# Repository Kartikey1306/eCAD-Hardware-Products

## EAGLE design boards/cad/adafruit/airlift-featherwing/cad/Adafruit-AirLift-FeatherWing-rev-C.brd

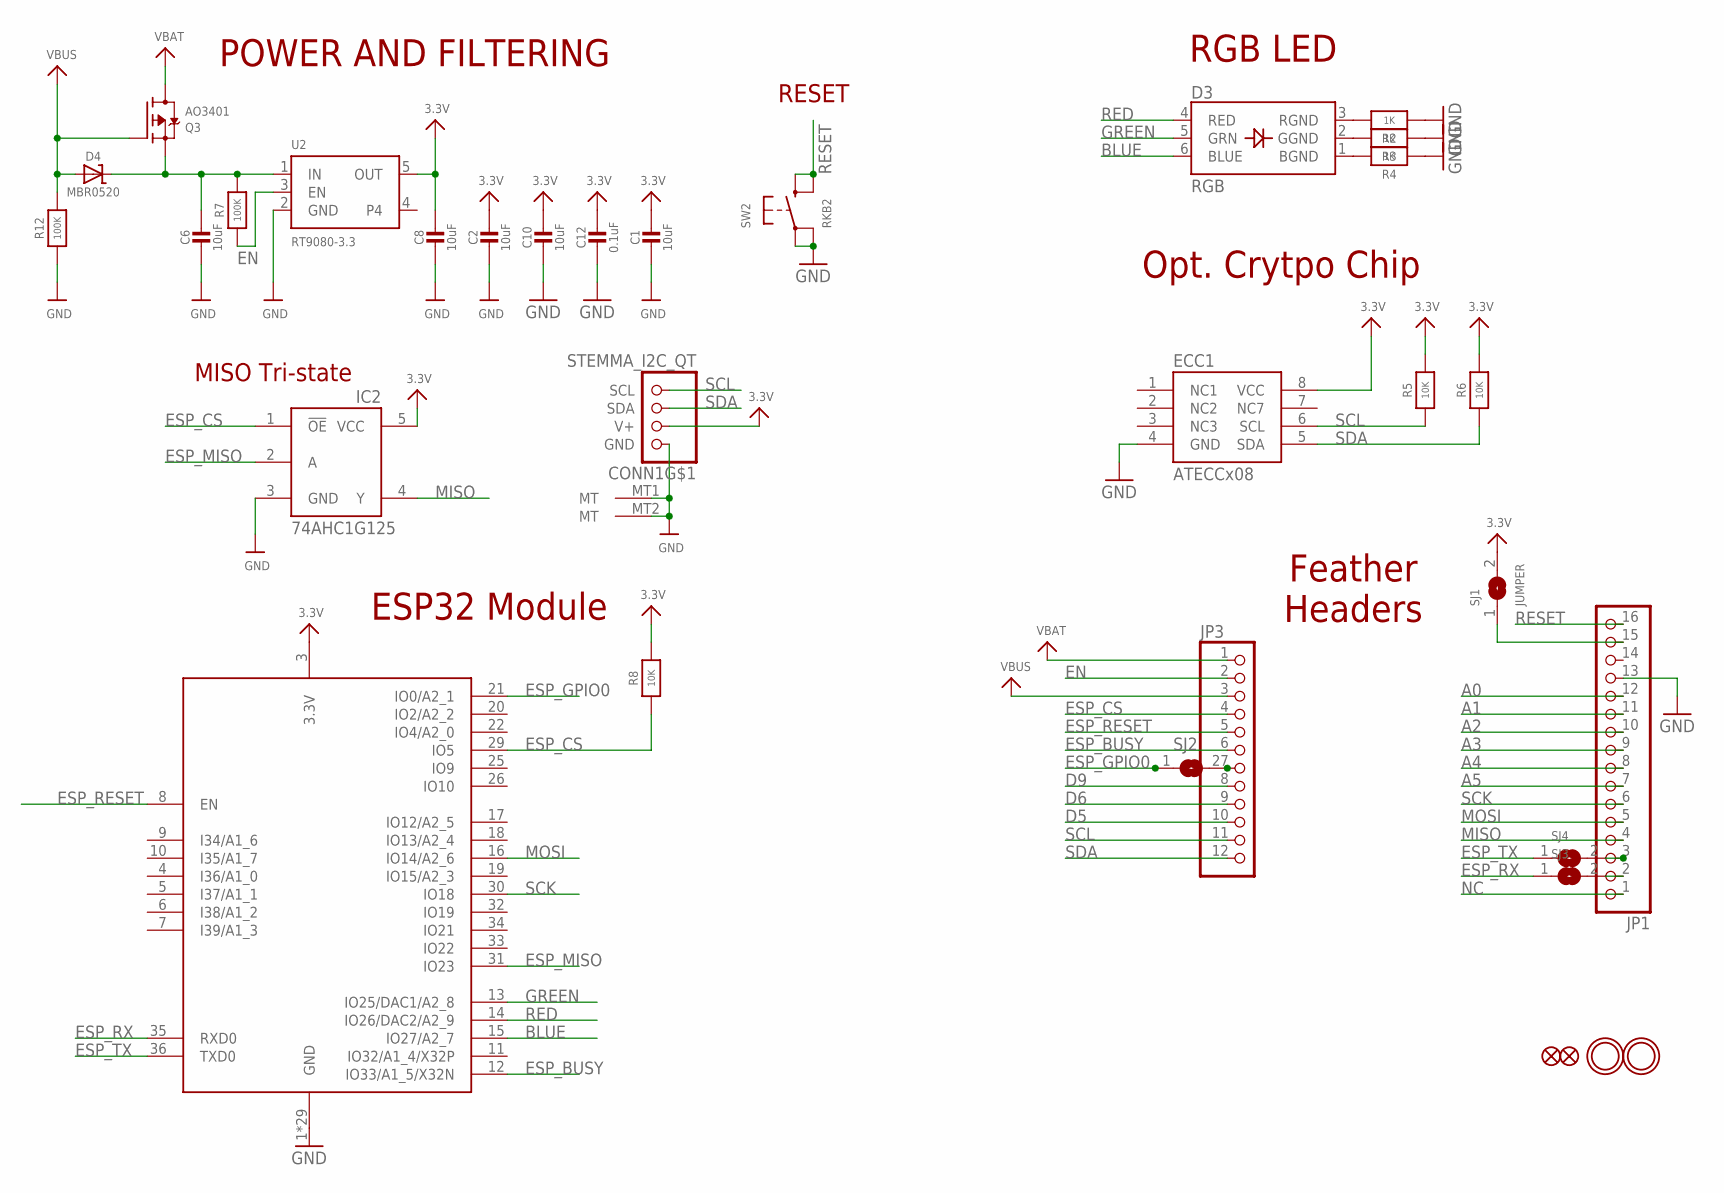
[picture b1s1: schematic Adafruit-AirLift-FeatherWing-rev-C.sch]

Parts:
C1, C2, C6, C8, C10: 10uF; 0805-NO
C12: 0.1uF; 0603-NO
CONN1: STEMMA_I2C_QT; JST_SH4
D3: RGB; RGBLED_3535_PLCC6
D4: MBR0520; SOD-123
ECC1: ATECCx08; SOIC8
IC2: 74AHC1G125; SOT23-5L
JP1: HEADER-1X16_MIN; 1X16_ROUND_MIN
JP3: HEADER-1X12_MIN; 1X12_ROUND_MIN
Q3: AO3401; SOT23-R
R2, R3, R4: 1K; 0603-NO
R5, R6, R8: 10K; 0603-NO
R7, R12: 100K; 0603-NO
SJ1: JUMPER; SOLDERJUMPER_ARROW_NOPASTE
SJ2, SJ3, SJ4: SOLDERJUMPER; SOLDERJUMPER_ARROW_NOPASTE
SW2: RKB2; BTN_RKB2_4.6X2.8
U2: RT9080-3.3; SOT23-5; JLC_ROTATION 0
U$31, U$32: MOUNTINGHOLE2.5; MOUNTINGHOLE_2.5_PLATED
U$34, U$35: FIDUCIAL_1MM
X1: ESP32-MINI-1

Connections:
3.3V: C1.1, C2.1, C8.1, C10.1, C12.1, CONN1.2 (V+), ECC1.8 (VCC), IC2.5 (VCC), R5.2, R6.2, R8.2, SJ1.2, U2.5 (OUT), X1.3 (3.3V)
A0: JP1.12
A1: JP1.11
A2: JP1.10
A3: JP1.9
A4: JP1.8
A5: JP1.7
BLUE: D3.6 (BLUE), X1.15 (IO27/A2_7)
D5: JP3.10
D6: JP3.9
D9: JP3.8
EN: JP3.2, R7.1, U2.3 (EN)
ESP_BUSY: JP3.6, X1.12 (IO33/A1_5/X32N)
ESP_CS: IC2.1 (!OE), JP3.4, R8.1, X1.29 (IO5)
ESP_GPIO0: SJ2.1, X1.21 (IO0/A2_1)
ESP_MISO: IC2.2 (A), X1.31 (IO23)
ESP_RESET: JP3.5, X1.8 (EN)
ESP_RX: SJ3.1, X1.35 (RXD0)
ESP_TX: SJ4.1, X1.36 (TXD0)
GND: C1.2, C2.2, C6.2, C8.2, C10.2, C12.2, CONN1.1 (GND), CONN1.MT1 (MT), CONN1.MT2 (MT), ECC1.4 (GND), IC2.3 (GND), JP1.13, R2.1, R3.1, R4.1, R12.1, SW2.A, SW2.A' (P1), U2.2 (GND), X1.1 (GND), X1.2 (GND), X1.27 (GND), X1.38 (GND), X1.39 (GND), X1.40 (GND), X1.41 (GND), X1.42 (GND), X1.43 (GND), X1.44 (GND), X1.45 (GND), X1.46 (GND), X1.47 (GND), X1.48 (GND), X1.49 (GND), X1.50 (GND), X1.51 (GND), X1.52 (GND), X1.53 (GND), X1.54 (GND), X1.55 (GND), X1.56 (GND), X1.57 (GND), X1.58 (GND), X1.59 (GND), X1.60 (GND), X1.61 (GND), X1.62 (GND), X1.63 (GND)
GREEN: D3.5 (GRN), X1.13 (IO25/DAC1/A2_8)
MISO: IC2.4 (Y), JP1.4
MOSI: JP1.5, X1.16 (IO14/A2_6)
unnamed: JP1.15, SJ1.1
unnamed: D3.3 (RGND), R2.2
unnamed: D3.2 (GGND), R3.2
unnamed: D3.1 (BGND), R4.2
unnamed: JP3.7, SJ2.2
unnamed: JP1.2, SJ3.2
unnamed: C6.1, D4.C, Q3.2 (S), R7.2, U2.1 (IN)
unnamed: JP1.3, SJ4.2
NC: JP1.1
RED: D3.4 (RED), X1.14 (IO26/DAC2/A2_9)
RESET: JP1.16, SW2.B (S), SW2.B' (S1)
SCK: JP1.6, X1.30 (IO18)
SCL: CONN1.4 (SCL), ECC1.6 (SCL), JP3.11, R5.1
SDA: CONN1.3 (SDA), ECC1.5 (SDA), JP3.12, R6.1
VBAT: JP3.1, Q3.3 (D)
VBUS: D4.A, JP3.3, Q3.1 (G), R12.2

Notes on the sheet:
POWER AND FILTERING
RESET
RGB LED
Opt. Crytpo Chip
Feather Headers
MISO Tri-state
ESP32 Module

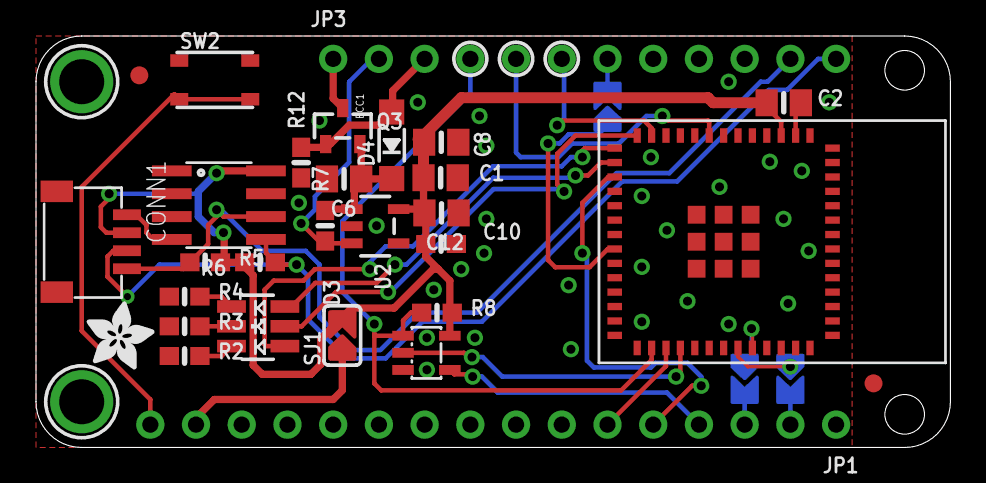
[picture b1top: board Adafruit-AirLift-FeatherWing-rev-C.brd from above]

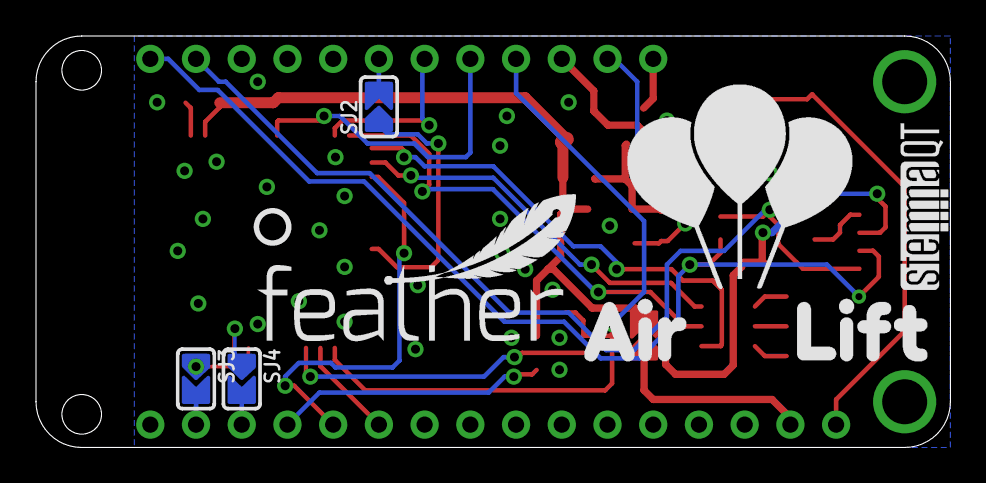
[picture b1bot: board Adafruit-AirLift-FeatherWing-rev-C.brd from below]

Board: 2 copper layers, 50.8 x 22.9 mm, 73 parts (21 on the bottom side), 29 nets.

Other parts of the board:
PLABEL0: PLABEL0
PLABEL1: PLABEL1
PLABEL2: PLABEL2
PLABEL3: PLABEL3
PLABEL4: PLABEL4
PLABEL5: PLABEL5
PLABEL6: PLABEL6
PLABEL7: PLABEL7
PLABEL8: PLABEL8
PLABEL9: PLABEL9
PLABEL10: PLABEL10
PLABEL11: PLABEL11
PLABEL12: PLABEL12
PLABEL13: PLABEL13
PLABEL14: PLABEL14
PLABEL15: PLABEL15
PLABEL16: PLABEL16
PLABEL17: PLABEL17
PLABEL18: PLABEL18
PLABEL19: PLABEL19
PLABEL20: PLABEL20
PLABEL21: PLABEL21
PLABEL22: PLABEL22
PLABEL23: PLABEL23
PLABEL24: PLABEL24
PLABEL25: PLABEL25
PLABEL26: PLABEL26
PLABEL27: PLABEL27
PLABEL28: PLABEL28
PLABEL29: PLABEL29
PLABEL30: PLABEL30
PLABEL31: PLABEL31
PLABEL32: PLABEL32
PLABEL33: PLABEL33
PLABEL34: PLABEL34
U$6: AIRLIFT
U$7: FEATHERLOGO_MED
U$12: STEMMAQT
U$13: PCBFEAT-REV-040
U$15: ADAFRUIT_3.5MM

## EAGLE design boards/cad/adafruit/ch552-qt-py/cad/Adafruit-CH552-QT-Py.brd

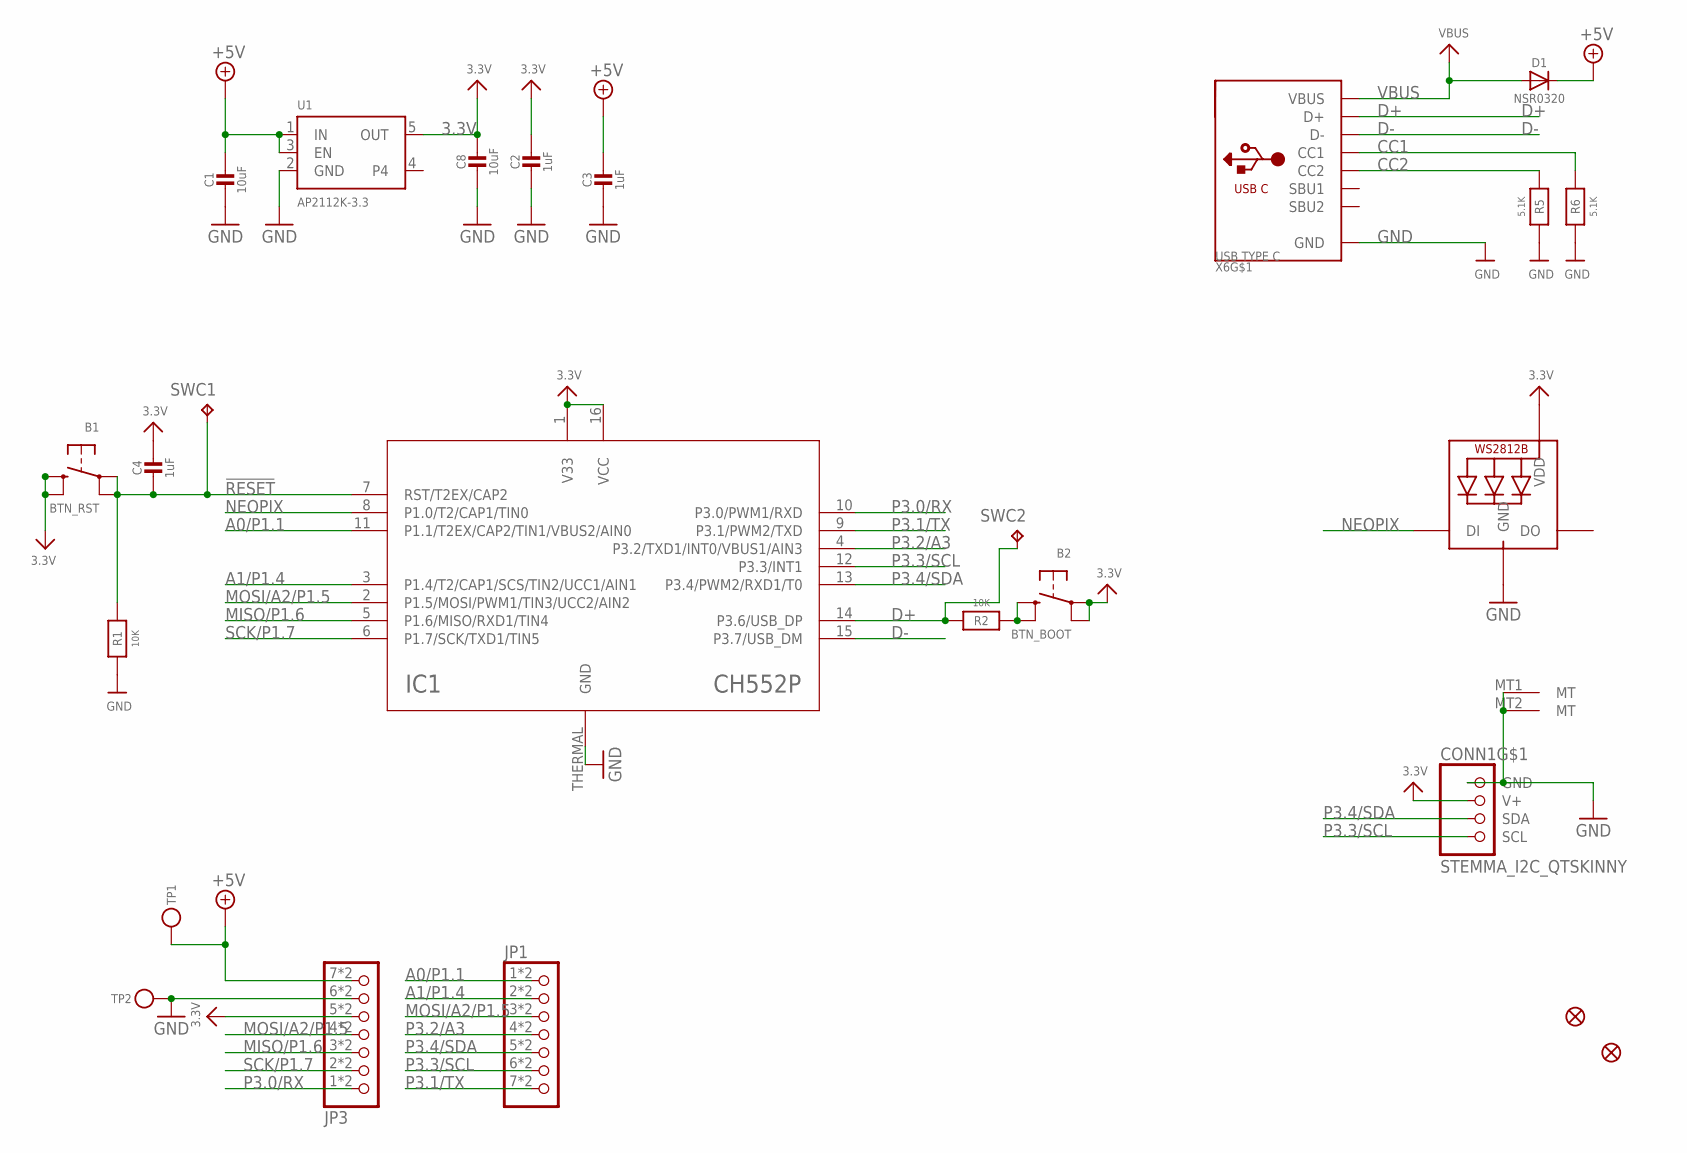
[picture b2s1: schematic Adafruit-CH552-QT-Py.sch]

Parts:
B1: BTN_RST; BTN_RKB2_4.6X2.8
B2: BTN_BOOT; BTN_RKB2_4.6X2.8
C1, C8: 10uF; _0805MP
C2, C3, C4: 1uF; _0402NO
CONN1: STEMMA_I2C_QTSKINNY; JST_SH4_SKINNY
D1: NSR0320; SOD-323_MINI
IC1: CH552PP; QFN16_3MM
JP1, JP3: HEADER-1X7_CASTEL; 1X07_CASTEL
LED1: WS2812B_SK6805_1515; SK6805_1515
R1, R2: 10K; _0402NO
R5, R6: 5.1K; _0402NO
SWC1: TPB1,27; B1,27
SWC2: TPTP15R; TP15R
TP1: TESTPOINT_PLUS13; TESTPOINT_PLUS_1X3MM
TP2: TESTPOINT_MINUS; TESTPOINT_MINUS_1X3MM
U1: AP2112K-3.3; SOT23-5
U$6, U$8: FIDUCIAL_1MM
X6: USB TYPE C; USB_C_CUSB31-CFM2AX-01-X

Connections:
3.3V: B1.B (S), B1.B' (S1), B2.A, B2.A' (P1), C2.1, C4.1, C8.1, CONN1.2 (V+), IC1.1 (V33), IC1.16 (VCC), JP3.5, JP3.5C (5), LED1.2 (VDD), U1.5 (OUT)
!RESET: B1.A, B1.A' (P1), C4.2, IC1.7 (RST/T2EX/CAP2), R1.2, SWC1.TP
+5V: C1.1, C3.1, D1.C, JP3.7, JP3.7C (7), TP1.P$1, U1.1 (IN), U1.3 (EN)
A0/P1.1: IC1.11 (P1.1/T2EX/CAP2/TIN1/VBUS2/AIN0), JP1.1, JP1.1C (1)
A1/P1.4: IC1.3 (P1.4/T2/CAP1/SCS/TIN2/UCC1/AIN1), JP1.2, JP1.2C (2)
CC1: R6.2, X6.A5 (CC1)
CC2: R5.2, X6.B5 (CC2)
D+: IC1.14 (P3.6/USB_DP), R2.2, SWC2.TP, X6.A6 (D+), X6.B6 (D+)
D-: IC1.15 (P3.7/USB_DM), X6.A7 (D-), X6.B7 (D-)
GND: C1.2, C2.2, C3.2, C8.2, CONN1.1 (GND), CONN1.MT1 (MT), CONN1.MT2 (MT), IC1.THERMAL (GND), JP3.6, JP3.6C (6), LED1.4 (GND), R1.1, R5.1, R6.1, TP2.P$1, U1.2 (GND), X6.A1B12 (GND), X6.B1A12 (GND)
MISO/P1.6: IC1.5 (P1.6/MISO/RXD1/TIN4), JP3.3, JP3.3C (3)
MOSI/A2/P1.5: IC1.2 (P1.5/MOSI/PWM1/TIN3/UCC2/AIN2), JP1.3, JP1.3C (3), JP3.4, JP3.4C (4)
unnamed: B2.B (S), B2.B' (S1), R2.1
NEOPIX: IC1.8 (P1.0/T2/CAP1/TIN0), LED1.1 (DI)
P3.0/RX: IC1.10 (P3.0/PWM1/RXD), JP3.1, JP3.1C (1)
P3.1/TX: IC1.9 (P3.1/PWM2/TXD), JP1.7, JP1.7C (7)
P3.2/A3: IC1.4 (P3.2/TXD1/INT0/VBUS1/AIN3), JP1.4, JP1.4C (4)
P3.3/SCL: CONN1.4 (SCL), IC1.12 (P3.3/INT1), JP1.6, JP1.6C (6)
P3.4/SDA: CONN1.3 (SDA), IC1.13 (P3.4/PWM2/RXD1/T0), JP1.5, JP1.5C (5)
SCK/P1.7: IC1.6 (P1.7/SCK/TXD1/TIN5), JP3.2, JP3.2C (2)
VBUS: D1.A, X6.A4B9 (VBUS), X6.B4A9 (VBUS)

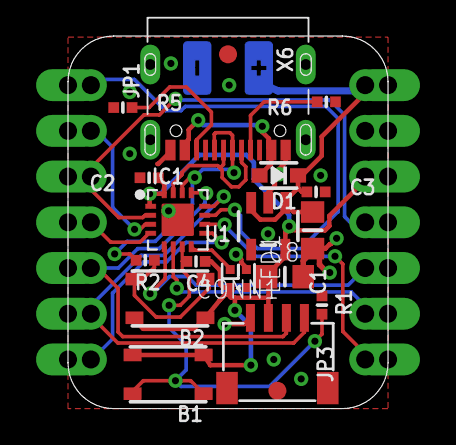
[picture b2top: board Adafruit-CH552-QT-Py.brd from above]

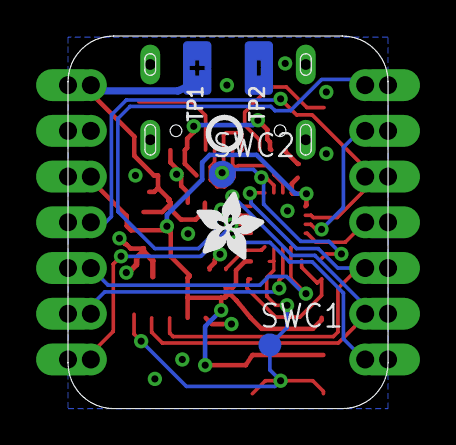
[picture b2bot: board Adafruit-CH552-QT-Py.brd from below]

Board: 2 copper layers, 17.8 x 20.7 mm, 44 parts (22 on the bottom side), 21 nets.

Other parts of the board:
PLABEL0: PLABEL0
PLABEL1: PLABEL1
PLABEL2: PLABEL2
PLABEL3: PLABEL3
PLABEL4: PLABEL4
PLABEL5: PLABEL5
PLABEL6: PLABEL6
PLABEL7: PLABEL7
PLABEL8: PLABEL8
PLABEL9: PLABEL9
PLABEL10: PLABEL10
PLABEL11: PLABEL11
PLABEL12: PLABEL12
PLABEL13: PLABEL13
PLABEL14: PLABEL14
U$11: ADAFRUIT_3.5MM
U$12: PCBFEAT-REV-040
U$13: QTPY_CH522_TOP
U$21: QTPY_CH552_BOT

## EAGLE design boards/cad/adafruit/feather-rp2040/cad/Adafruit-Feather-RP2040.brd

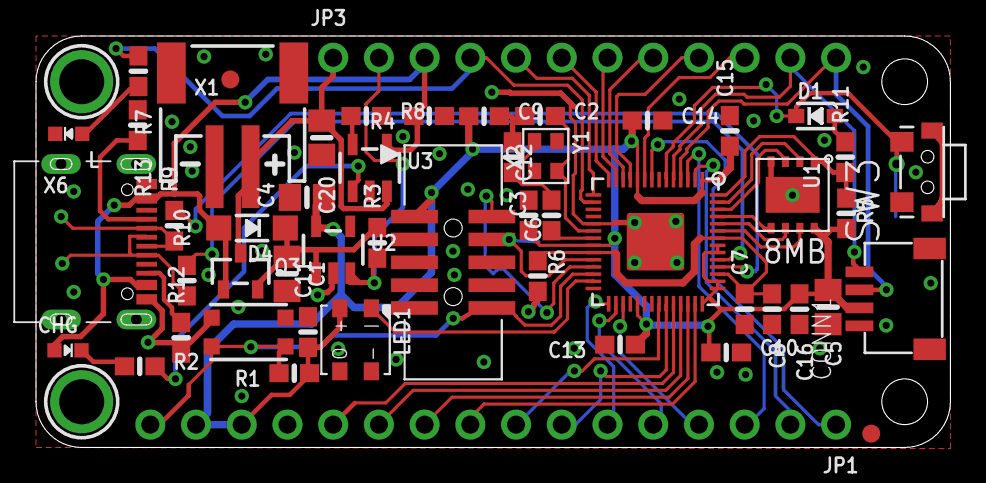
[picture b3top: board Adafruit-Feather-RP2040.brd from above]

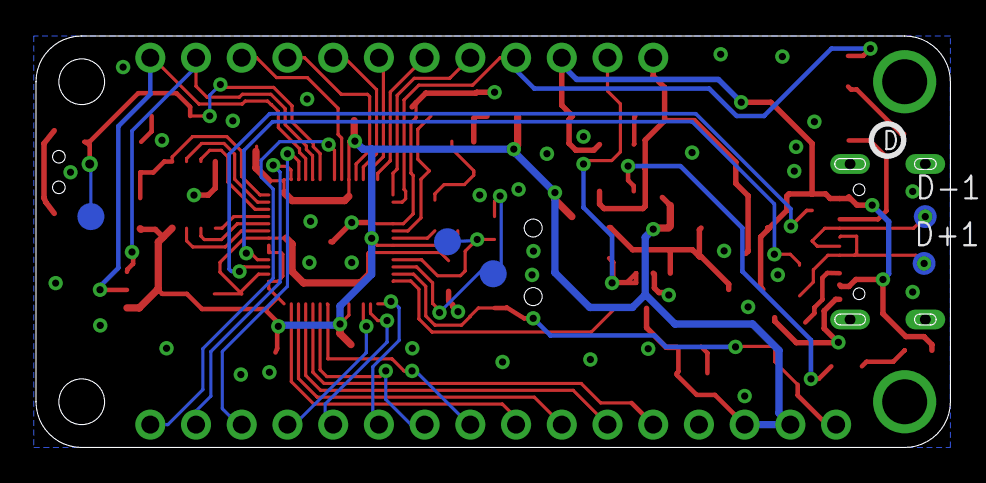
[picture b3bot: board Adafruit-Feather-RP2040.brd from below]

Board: 2 copper layers, 50.8 x 22.9 mm, 61 parts (7 on the bottom side), 53 nets.

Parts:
C1, C4, C5, C20: 10uF; 0805-NO
C2, C3: 22pF; 0603-NO
C6, C7, C9, C11, C12, C13, C14, C15, C16: 0.1uF; 0603-NO
C8, C10: 1uF; 0603-NO
CHG: ORANGE; CHIPLED_0603_NOOUTLINE
CONN1: STEMMA_I2C_QT; JST_SH4
D1: NSR0320; SOD-323_MINI
D4: MBR0540; SOD-123
D+1: TPB1,27; B1,27
D-1: TPB1,27; B1,27
IC1: RP2040_QFN56; QFN56_7MM_REDUCEDEPAD
JP1: 1X16_ROUND
JP3: 1X12_ROUND
L: RED; CHIPLED_0603_NOOUTLINE
LED1: WS2812B3535; LED3535
Q3: DMG3415; SOT23-R
R1, R2, R3, R4, R5, R7: 10K; 0603-NO
R6, R11: 1K; 0603-NO
R8, R12, R13: 5.1K; 0603-NO
R9, R10: 27; 0603-NO
SW1: KMR2; BTN_KMR2_4.6X2.8
SW3: Mini RA Switch; SPST_TACTILE_RA_2*4*3.5MM
TP1, TP2, TP3: TESTPOINT_ROUND_1.5MM_NO
U1: W25Q64JVSSIQ; USON8_4X4
U2: RT9080/AP2112-3.3; SOT23-5
U3: MCP73831T-2ACI/OT; SOT23-5
U$1: RP2040_BOT
U$13: PCBFEAT-REV-040
U$31, U$32: MOUNTINGHOLE2.5; MOUNTINGHOLE_2.5_PLATED
U$34, U$35: FIDUCIAL_1MM
U$43: RP2040_TOP
X1: JSTPH; JSTPH2_BATT
X2: 2x5 SWD; 2X05_1.27MM_BOX_NOCREAM
X6: USB Type C; USB_C_CUSB31-CFM2AX-01-X
Y1: 12MHz/12pF; CRYSTAL_2.5X2

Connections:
1.2V: C6.2, C7.2, C8.1, IC1.23, IC1.45, IC1.50
!RESET: IC1.26, JP1.16, R1.2, SW1.A, SW1.A', X2.10
+3V3: C4.1, C5.1, C9.1, C10.1, C11.1, C12.1, C13.1, C14.1, C15.1, C16.1, CONN1.2, IC1.1, IC1.10, IC1.22, IC1.33, IC1.42, IC1.43, IC1.44, IC1.48, IC1.49, JP1.14, JP1.15, LED1.2, R1.1, R5.2, U1.8, U2.5, X2.1
A0: IC1.38, JP1.12
A1: IC1.39, JP1.11
A2: IC1.40, JP1.10
A3: IC1.41, JP1.9
CC1: R13.2, X6.A5
CC2: R12.2, X6.B5
D4: IC1.8, JP1.1
D5: IC1.9, JP3.10
D6: IC1.11, JP3.9
D9: IC1.12, JP3.8
D10: IC1.13, JP3.7
D11: IC1.14, JP3.6
D12: IC1.15, JP3.5
D13: IC1.16, JP3.4, R7.1
D24: IC1.36, JP1.8
D25: IC1.37, JP1.7
D+: IC1.47, R10.2
D-: IC1.46, R9.2
EN: JP3.2, R3.1, U2.3
GND: C1.2, C2.1, C3.1, C4.2, C5.2, C6.1, C7.1, C8.2, C9.2, C10.2, C11.2, C12.2, C13.2, C14.2, C15.2, C16.2, C20.2, CONN1.1, CONN1.MT1, CONN1.MT2, IC1.19, IC1.P$1, JP1.13, L.C, LED1.4, R4.1, R8.2, R12.1, R13.1, SW1.B, SW1.B', SW3.1, SW3.MT1, SW3.MT2, U1.4, U1.PAD, U2.2, U3.2, X1.1, X1.NC1, X1.NC2, X2.3, X2.5, X2.7, X2.9, X6.A1B12, X6.B1A12
MISO: IC1.31, JP1.4
MOSI: IC1.30, JP1.5
unnamed: CHG.C, R2.1
unnamed: L.A, R7.2
unnamed: R2.2, U3.1
unnamed: R8.1, U3.5
unnamed: C2.2, IC1.20, Y1.3
unnamed: C3.2, R6.1, Y1.1
unnamed: IC1.21, R6.2
unnamed: D1.A, R11.2
NEOPIX: IC1.27, LED1.1
QSPI_CS: IC1.56, R5.1, R11.1, U1.1
QSPI_DATA[0]: IC1.53, U1.5
QSPI_DATA[1]: IC1.55, U1.2
QSPI_DATA[2]: IC1.54, U1.3
QSPI_DATA[3]: IC1.51, U1.7
QSPI_SCK: IC1.52, U1.6
RX: IC1.3, JP1.3
SCK: IC1.29, JP1.6
SCL: CONN1.4, IC1.5, JP3.11
SDA: CONN1.3, IC1.4, JP3.12
SWCLK: IC1.24, TP2.P$1, X2.4
SWDIO: IC1.25, TP1.P$1, X2.2
TX: IC1.2, JP1.2
USBBOOT: D1.C, IC1.6, SW3.2, TP3.P$1
USB_D+: D+1.TP, R10.1, X6.A6, X6.B6
USB_D-: D-1.TP, R9.1, X6.A7, X6.B7
VBAT: C20.1, JP3.1, Q3.3, U3.3, X1.2
VBUS: CHG.A, D4.A, JP3.3, Q3.1, R4.2, U3.4, X6.A4B9, X6.B4A9
VHI: C1.1, D4.C, Q3.2, R3.2, U2.1

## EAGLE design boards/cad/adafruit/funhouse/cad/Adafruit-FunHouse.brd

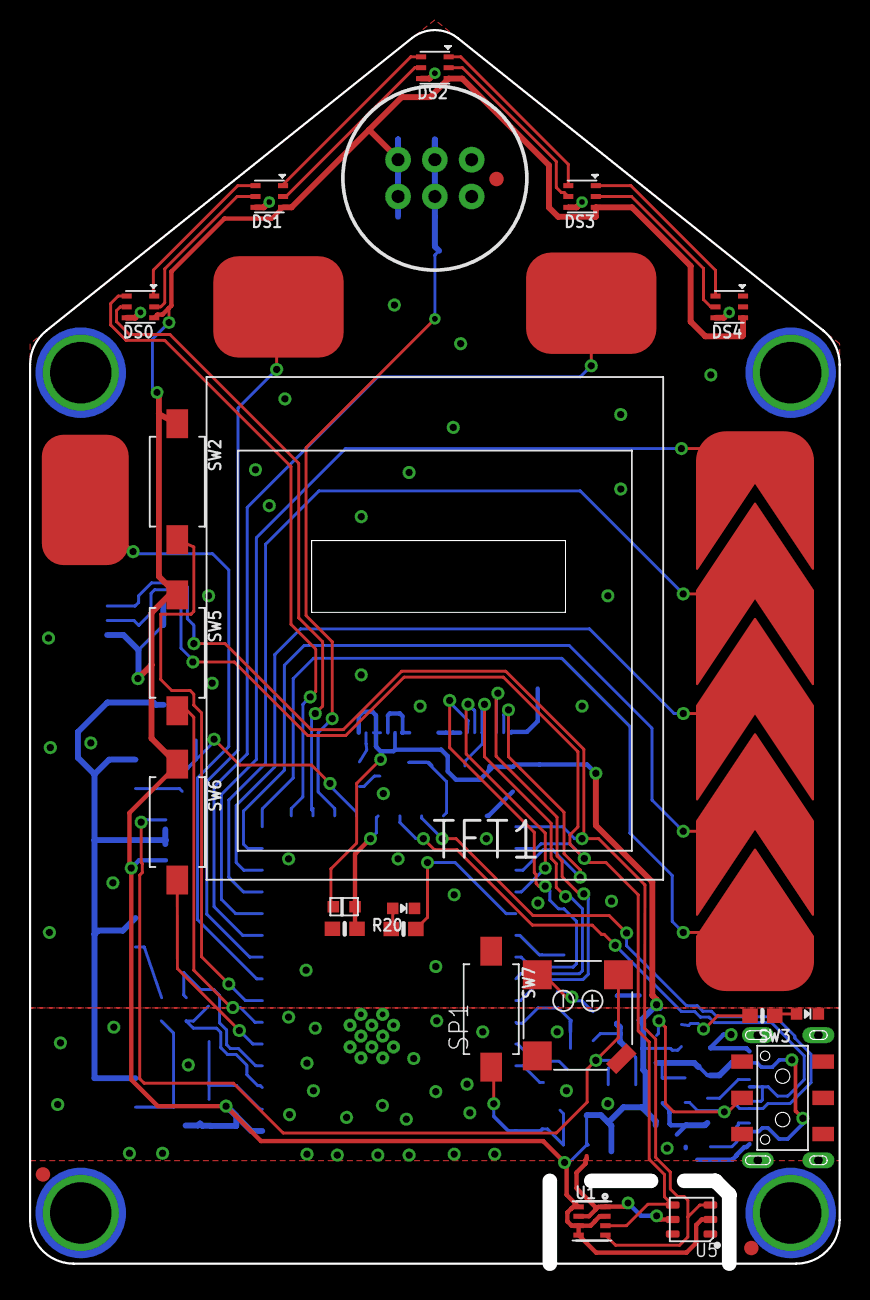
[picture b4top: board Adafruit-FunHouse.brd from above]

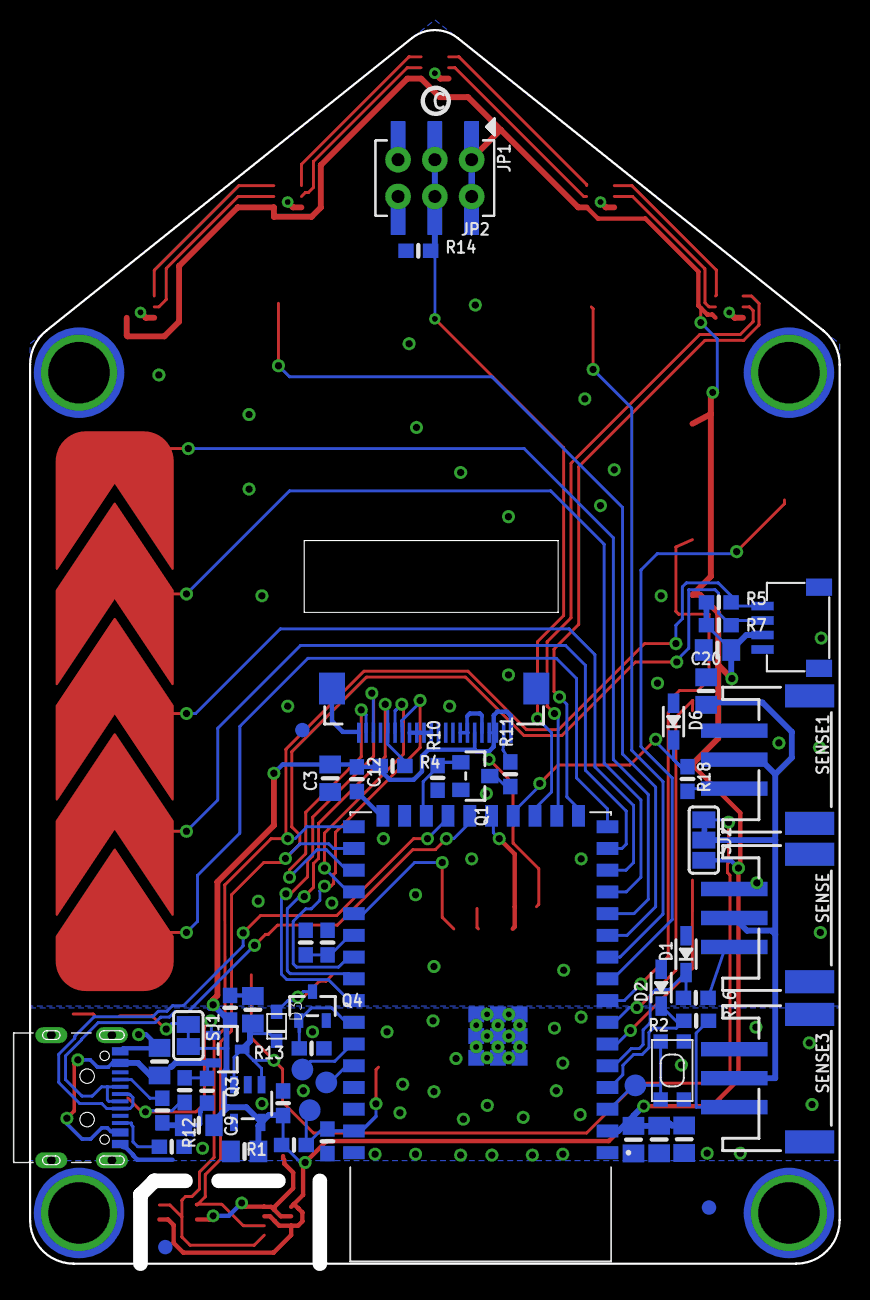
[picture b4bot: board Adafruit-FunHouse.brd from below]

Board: 2 copper layers, 55.9 x 85.1 mm, 91 parts (63 on the bottom side), 60 nets.

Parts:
C1, C20: 10uF; 0805-NO
C2, C5, C15: 0.1uF; 0603-NO
C3, C4, C7, C10, C11, C13, C17: 10µF; 0805-NO
C6, C12, C14: 1uF; 0603-NO
C9: 10uF/10V+; 0805_10MGAP
CONN1: STEMMA_I2C_QT; JST_SH4
D1, D2, D6: 3.6V; SOD-323
D3: 1N4148; SOD-323F
DS0, DS1, DS2, DS3, DS4: APA102-2020; APA102_2020
FID1, FID2, FID3, FID4, FID5, FID6: FIDUCIAL_1MM
JP1: 2x3 SMT; 2X03_SMT_4UCON_14113
JP2: 2X03_SMTTHM
L: RED; CHIPLED_0603_NOOUTLINE
ON: GREEN; CHIPLED_0603_NOOUTLINE
Q1: BSS138; SOT23-WIDE
Q3: DMG3415U-7; SOT23-R
Q4: BSS138; SOT23-R
R1, R4, R5, R7, R9, R10, R12, R13, R20: 10K; 0603-NO
R2, R16, R18: 1K; 0603-NO
R3, R8: 5.1K; 0603-NO
R6: 47K; 0603-NO
R11: 100; 0603-NO
R14, R17: 1Meg; 0603-NO
SENSE, SENSE1, SENSE3: JST PH 3; JSTPH3
SJ1: SOLDERJUMPER_CLOSEDWIRE
SJ2: SOLDERJUMPER_2WAY_OPEN_NOPASTE
SP1: 7.5mm SPK; BUZZER_SMT_7.5MM
SW2, SW5, SW6, SW7: FSM2JMTR; TACTILE_3X6MM
SW3: EG1390
SW4: SPST_TACT-KMR2; KMR2
TFT1: DISP_TFT_1.54IN_240X240_22P; TFT_1.54IN_240X240_22PIN
TP1, TP2, TP3, TP6: TESTPOINT_ROUND_1.5MM_NO
TP4, TP5, TP7, TP8: SEWTAP_SMTNUTM3; SMT_NUT_3MM
U1: DPS3; BMX280_COMBO
U2: ALS-PT19; ALS-PT19-315C
U3: ESP32-S2-MODULE_WROVER; MODULE_ESP32-S2-WROVER
U4: AP2112K-3.3; SOT23-5
U5: AHT20; SNR6-1.0-3X3X1MM
U$41: PCBFEAT-REV-040
U$45: FUNHOUSE_FRONT
U$69: FUNHOUSE_BACK
X1: CAPTOUCH_10MM; CAPTOUCH_6X9MM
X3, X5: CAPTOUCH_10MM; CAPTOUCH_7X9MM
X4: USB C; USB_C_CUSB31-CFM2AX-01-X
X6: CAPTOUCH_5SLIDER_10MM; CAPTOUCH_5SLIDER

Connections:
3.3V: C2.1, C3.1, C4.1, C5.1, C7.1, C9.2, C10.1, C12.1, C13.1, C17.1, CONN1.2, DS0.3, DS1.3, DS2.3, DS3.3, DS4.3, JP1.1, JP1.2, JP2.1, JP2.2, JP2.T1, JP2.T2, R1.2, R4.1, R5.1, R7.1, SJ1.2, SJ2.3, SW2.P$1, SW5.P$1, SW6.P$1, TFT1.1, TFT1.3, TFT1.4, TFT1.6, U1.2, U1.5, U1.6, U1.8, U2.C, U3.2, U4.5, U5.2
A0_JST: R18.1, SENSE1.3
A2_JST2: R2.1, SENSE3.3
AD0: D6.C, R18.2, U3.20
AD1: D1.C, R16.2, U3.5
AD1_JST: R16.1, SENSE.3
AD2: D2.C, R2.2, U3.4
BOOT0: SW4.2, SW4.4, TP1.P$1, U3.3
BUTTON_DOWN: SW6.P$2, U3.6
BUTTON_SEL: SW5.P$2, U3.7
BUTTON_UP: SW2.P$2, U3.8
CC1: R8.2, X4.A5
CC2: R3.2, X4.B5
CT6: U3.9, X1.P$1
CT7: U3.10, X3.P$1
CT8: U3.11, X5.P$1
CT9: U3.12, X6.P$5
CT10: U3.13, X6.P$4
CT11: U3.14, X6.P$3
CT12: U3.15, X6.P$2
CT13: U3.16, X6.P$1
D+: U3.23, X4.A6, X4.B6
D-: U3.22, X4.A7, X4.B7
DS_CLK: DS0.5, U3.18
DS_DATA: DS0.6, U3.17
EN: Q3.1, R12.2, SW3.P2
GND: C1.2, C2.2, C3.2, C4.2, C5.2, C6.2, C7.2, C9.1, C10.2, C11.2, C12.2, C13.2, C14.2, C15.2, C17.2, C20.2, CONN1.1, CONN1.MT1, CONN1.MT2, D1.A, D2.A, D6.A, DS0.4, DS1.4, DS2.4, DS3.4, DS4.4, JP1.5, JP1.6, JP2.5, JP2.6, JP2.T5, JP2.T6, L.C, ON.C, Q1.2, Q4.2, R3.1, R8.1, R10.1, R13.1, R14.1, R17.1, R20.1, SENSE.1, SENSE.NC1, SENSE.NC2, SENSE1.1, SENSE1.NC1, SENSE1.NC2, SENSE3.1, SENSE3.NC1, SENSE3.NC2, SW3.O1, SW3.O2, SW3.P1, SW3.S1, SW4.1, SW4.3, SW7.P$1, TFT1.5, TFT1.7, TFT1.8, TFT1.9, TFT1.10, TFT1.11, TFT1.12, TFT1.13, TFT1.14, TFT1.15, TFT1.22, TFT1.SUPPORT1, TFT1.SUPPORT2, U1.1, U1.7, U3.1, U3.26, U3.42, U3.43_1, U3.43_2, U3.43_3, U3.43_4, U3.43_5, U3.43_6, U3.43_7, U3.43_8, U3.43_9, U3.43_10, U3.43_11, U3.43_12, U3.43_13, U3.43_14, U3.43_15, U3.43_16, U3.43_17, U3.43_18, U3.43_19, U3.43_20, U3.43_21, U4.2, U5.5, X4.A1B12, X4.B1A12
IO38_DOUBLETAP: C6.1, R17.2, U3.32
LIGHT: R20.2, U2.E, U3.21
MISO: R9.2, U3.31
MOSI: TFT1.21, U3.29
unnamed: L.A, R9.1
unnamed: R6.2, SJ1.1
unnamed: ON.A, R6.1
unnamed: D3.A, Q4.3, SP1.-
unnamed: DS0.1, DS1.6
unnamed: DS0.2, DS1.5
unnamed: DS1.1, DS2.6
unnamed: DS1.2, DS2.5
unnamed: DS2.1, DS3.6
unnamed: DS2.2, DS3.5
unnamed: DS3.1, DS4.6
unnamed: DS3.2, DS4.5
unnamed: Q1.3, R11.1
PIR_SENSE: JP1.3, JP1.4, JP2.3, JP2.4, JP2.T3, JP2.T4, R14.2, U3.19
RESET: C14.1, R1.1, SW7.P$2, TP6.P$1, U3.41
RXD0: TP2.P$1, U3.38
SCK: TFT1.17, U3.30
SCL: CONN1.4, R5.2, U1.4, U3.27, U5.3
SDA: CONN1.3, R7.2, U1.3, U3.28, U5.4
SPKR: Q4.1, R13.2, U3.36
TFT_CS: R4.2, TFT1.18, U3.34
TFT_DC: TFT1.16, U3.33
TFT_LEDK: R11.2, TFT1.2
TFT_LITE: Q1.1, R10.2, U3.24
TFT_RESET: TFT1.20, U3.35
TXD0: TP3.P$1, U3.37
VBUS: C1.1, C15.1, Q3.2, R12.1, X4.A4B9, X4.B4A9
VCC: C20.1, SENSE.2, SENSE1.2, SENSE3.2, SJ2.2
VHIGH: C11.1, D3.C, Q3.3, SJ2.1, SP1.+, U4.1, U4.3

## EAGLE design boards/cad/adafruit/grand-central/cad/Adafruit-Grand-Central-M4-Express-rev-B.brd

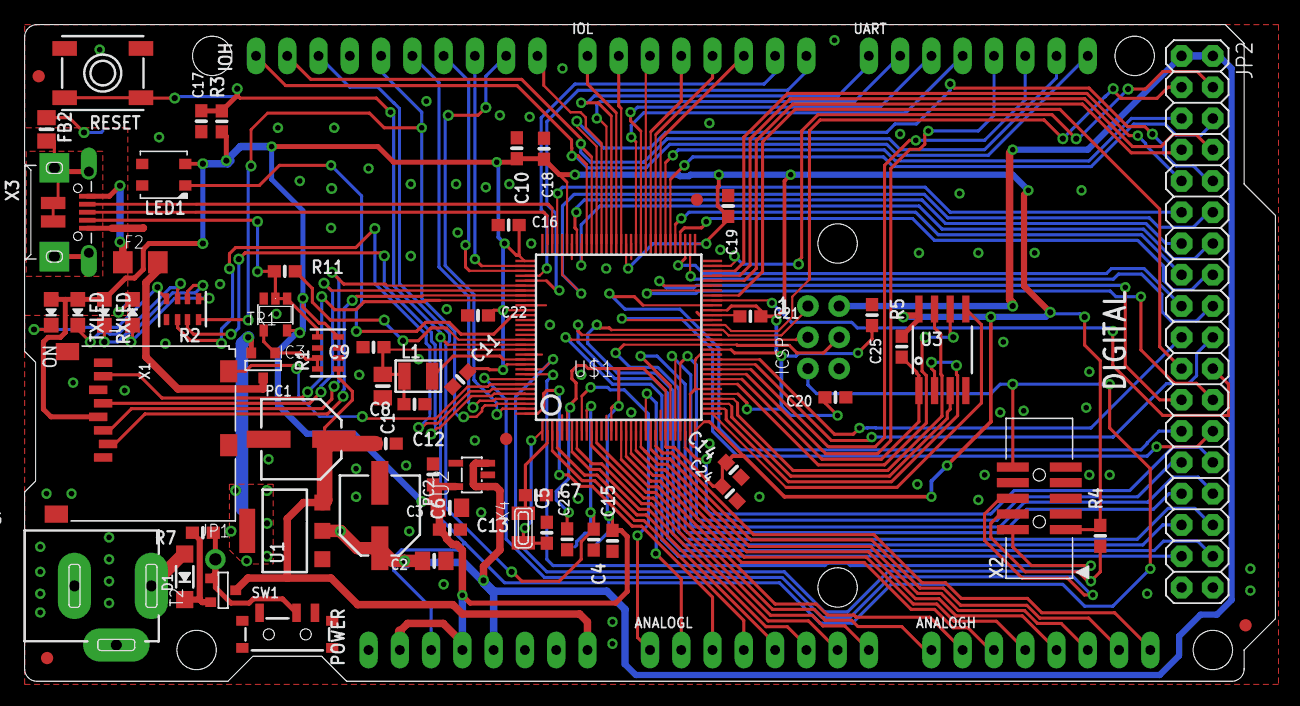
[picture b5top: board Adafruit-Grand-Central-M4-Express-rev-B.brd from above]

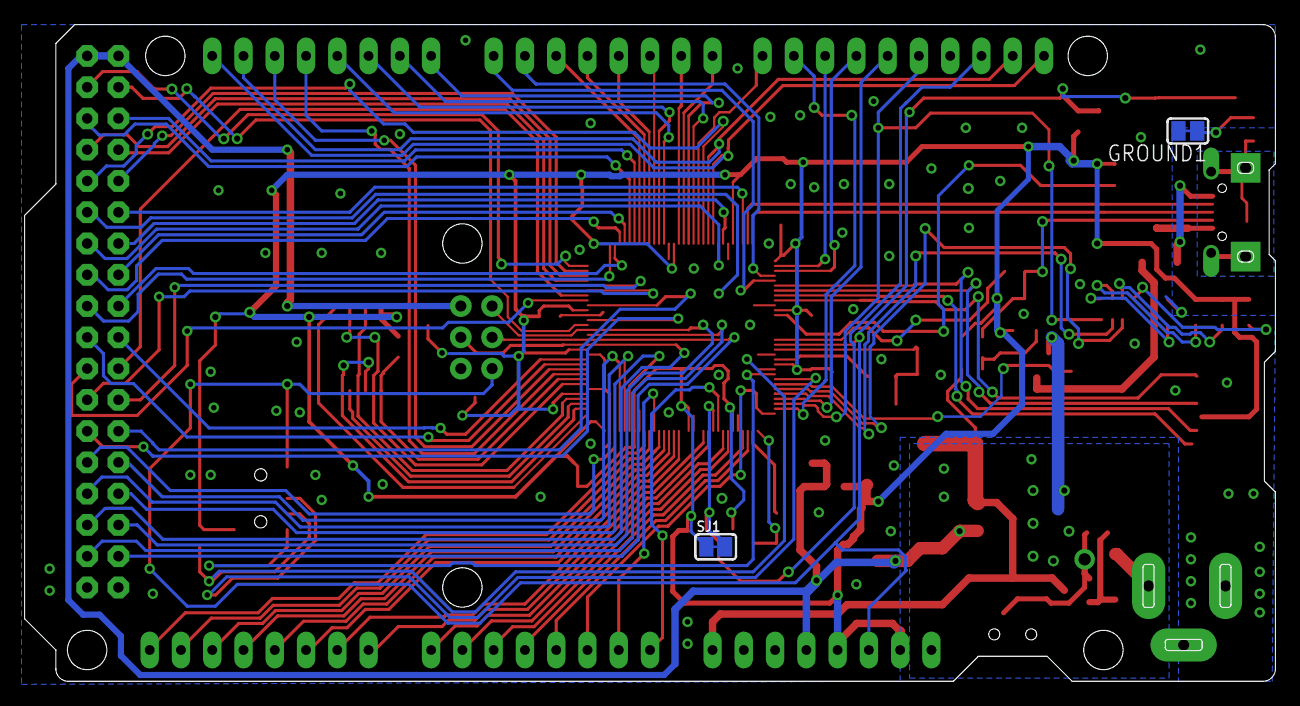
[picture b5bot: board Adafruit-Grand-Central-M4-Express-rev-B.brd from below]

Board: 2 copper layers, 101.6 x 53.3 mm, 75 parts (3 on the bottom side), 113 nets.

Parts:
ANALOGH: 20610; 1X08_OVALWAVE
ANALOGL: 20610; 1X08_OVALWAVE
C1, C2, C3: 10uF; 0805-NO
C4, C6, C8, C10, C11, C14, C15, C16, C18, C19, C20, C21, C22, C23, C24, C25: .1u; 0603-NO
C5, C7: 22pF; 0603-NO
C9: 1uF; 0603-NO
C12, C13, C17: 0.1uF; 0603-NO
D1: MBR120; SOD-123
F2: 500mA; R1206
FB2: FERRITE; 0805-NO
FD1, FD2, FD3, FD4, FD5: FIDUCIAL_1MM
GROUND1: SOLDERJUMPER_CLOSEDWIRE
IC3: 74LVC1G125D; SOT23-5
ICSP: 3x2 M; 2X03_ROUND_70MIL
IOH: 20611; 1X10_OVALWAVE
IOL: 20610; 1X08_OVALWAVE
JP1: 1X01_ROUND
JP2: 2X18_THICKWAVE
L: RED; CHIPLED_0805_NOOUTLINE
L1: 10uH; INDUCTOR_1007
LED1: WS2812B3535; LED3535
ON: GREEN; CHIPLED_0805_NOOUTLINE
PC1: 47uF/25V; PANASONIC_D
PC2: 47uF+/6.3V+; PANASONIC_D
POWER: 20610; 1X08_OVALWAVE
R1: 100K; RESPACK_4X0603
R2: 1K; RESPACK_4X0603
R3, R5, R7: 10K; 0603-NO
R4: 1K; 0603-NO
R11: 330R; 0603-NO
RESET: EVQQ 6mm; EVQ-Q2_SMALLER
RXLED: YELLOW; CHIPLED_0805_NOOUTLINE
SJ1: AREF_3V; SOLDERJUMPER_CLOSEDWIRE
SW1: SPDT_SMT_SSSS811101
T2: DMP3098L-7; SOT-23
TR1: DMP3098L-7; SOT-23
TXLED: YELLOW; CHIPLED_0805_NOOUTLINE
U1: NCP1117ST50T3G; SOT223-R
U2: AP2112K-3.3; SOT23-DBV
U3: GD25Q64; SOIC8_208MIL
U$1: SAMD51PXXA; SQFP-S-14X14-128
U$23: GRANDCENTRAL_REVB-BOT
U$30: GRANDCENTRAL_REVB_TOP
UART: 20610; 1X08_OVALWAVE
X1: microsd; MICROSD
X2: 2x5 0.05" SWD; 2X05_1.27MM_BOX_POSTS
X3: 20329; 4UCONN_20329_V2
X4: 32.768; XTAL3215
X5: 2.1mm; DCJACK_2MM_PTH

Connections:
3.3V: C3.2, C6.2, C10.2, C11.2, C13.1, C14.2, C15.2, C16.2, C18.2, C19.2, C20.2, C21.2, C22.2, C23.2, C24.2, C25.2, IC3.5, LED1.2, ON.A, POWER.2, POWER.4, R1.4, R3.1, R4.2, R5.2, RXLED.A, SJ1.1, TXLED.A, U2.5, U3.8, U$1.6, U$1.15, U$1.26, U$1.32, U$1.37, U$1.46, U$1.54, U$1.65, U$1.79, U$1.91, U$1.97, U$1.107, U$1.118, X1.4, X2.1
!RESET: C17.2, ICSP.5, POWER.3, R3.2, RESET.B, RESET.B', U$1.114, X2.10
+5V: C2.2, ICSP.2, JP2.1, JP2.2, PC2.+, POWER.5, TR1.2, U1.2, U1.4, U2.1, U2.3
A0: ANALOGL.1, U$1.9
A1: ANALOGL.2, U$1.22
A2: ANALOGL.3, U$1.128
A3: ANALOGL.4, U$1.3
A4: ANALOGL.5, U$1.4
A5: ANALOGL.6, U$1.7
A6: ANALOGL.7, U$1.8
A7: ANALOGL.8, U$1.11
A8: ANALOGH.1, U$1.12
A9: ANALOGH.2, U$1.17
A10: ANALOGH.3, U$1.18
A11: ANALOGH.4, U$1.19
A12: ANALOGH.5, U$1.20
A13: ANALOGH.6, U$1.21
A14: ANALOGH.7, U$1.23
A15: ANALOGH.8, U$1.24
AREF: C4.1, IOH.3, SJ1.2, U$1.10
D0: IOL.8, U$1.101
D1: IOL.7, U$1.100
D2: IOL.6, U$1.72
D3: IOL.5, U$1.73
D4: IOL.4, U$1.74
D5: IOL.3, U$1.75
D6: IOL.2, U$1.80
D7: IOL.1, U$1.81
D8: IOH.10, U$1.84
D9: IOH.9, U$1.127
D10: IOH.8, U$1.98
D11: IOH.7, U$1.99
D12: IOH.6, U$1.125
D13: IOH.5, R2.8, U$1.126
D22: JP2.3, U$1.51
D23: JP2.4, U$1.63
D44: JP2.25, U$1.55
D45: JP2.26, U$1.52
D46: JP2.27, U$1.29
D47: JP2.28, U$1.30
D48: JP2.29, U$1.27
D49: JP2.30, U$1.28
D+: U$1.95, X3.D+
D-: U$1.94, X3.D-
FLASH_CS: R5.1, U3.1, U$1.40
FLASH_IO0: U3.5, U$1.33
FLASH_IO1: U3.2, U$1.34
FLASH_IO2: U3.3, U$1.35
FLASH_IO3: U3.7, U$1.36
FLASH_SCK: U3.6, U$1.39
GND: C1.2, C2.1, C3.1, C4.2, C5.2, C6.1, C7.2, C8.1, C9.2, C10.1, C11.1, C12.2, C13.2, C14.1, C15.1, C16.1, C17.1, C18.1, C19.1, C20.1, C21.1, C22.1, C23.1, C24.1, C25.1, GROUND1.2, IC3.3, ICSP.6, IOH.4, JP2.35, JP2.36, L.C, LED1.4, PC1.-, PC2.-, POWER.6, POWER.7, R1.2, R2.5, RESET.A, RESET.A', SW1.A, U1.1, U2.2, U3.4, U$1.5, U$1.14, U$1.25, U$1.31, U$1.38, U$1.45, U$1.53, U$1.64, U$1.78, U$1.90, U$1.96, U$1.106, U$1.116, X1.6, X1.MT1, X1.MT2, X2.3, X2.5, X3.GND, X5.GND, X5.GNDBREAK
MISO: ICSP.1, JP2.31, U$1.50
MOSI: ICSP.4, JP2.32, U$1.47
unnamed: L.A, R2.1
unnamed: FB2.1, GROUND1.1
unnamed: ON.C, R2.4
unnamed: L1.P$2, U$1.117
unnamed: R2.2, RXLED.C
unnamed: R2.3, TXLED.C
unnamed: C5.1, U$1.1, X4.P$1
unnamed: IC3.1, IC3.2, R1.5, R11.1, X3.ID
unnamed: IC3.4, R1.7, R1.8, TR1.3
unnamed: C7.1, U$1.2, X4.P$2
unnamed: D1.C, R7.2, T2.2
NEOPIX: LED1.1, U$1.108
PCC_CLK: JP2.9, U$1.62
PCC_D0: JP2.18, U$1.66
PCC_D1: JP2.17, U$1.67
PCC_D2: JP2.16, U$1.68
PCC_D3: JP2.15, U$1.69
PCC_D4: JP2.14, U$1.88
PCC_D5: JP2.13, U$1.89
PCC_D6: JP2.12, U$1.92
PCC_D7: JP2.11, U$1.93
PCC_D8: JP2.20, U$1.43
PCC_D9: JP2.19, U$1.44
PCC_D10: JP2.22, U$1.56
PCC_D11: JP2.21, U$1.57
PCC_D12: JP2.24, U$1.58
PCC_D13: JP2.23, U$1.59
PCC_DEN1: JP2.7, U$1.60
PCC_DEN2: JP2.8, U$1.61
PCC_XCLK: JP2.10, U$1.85
PWRIN: D1.A, X5.PWR
PWR_SWITCH: JP1.1, R7.1, SW1.B, T2.3
RXLED: R2.7, U$1.124
SCK: ICSP.3, JP2.33, U$1.48
SCL: IOH.1, U$1.87, UART.8
SCL_1: JP2.5, U$1.71
SDA: IOH.2, U$1.86, UART.7
SDA_1: JP2.6, U$1.70
SD_CD: U$1.122, X1.CD1
SD_CS: U$1.104, X1.2
SD_MISO: U$1.105, X1.7
SD_MOSI: U$1.102, X1.3
SD_SCK: U$1.103, X1.5
SS: JP2.34, U$1.49
SWCLK: R4.1, U$1.119, X2.4
SWDIO: U$1.120, X2.2
SWO: U$1.121, X2.6
TXLED: R2.6, U$1.123
UART1_RX: U$1.42, UART.6
UART1_TX: U$1.41, UART.5
UART2_RX: U$1.77, UART.4
UART2_TX: U$1.76, UART.3
UART3_RX: U$1.83, UART.2
UART3_TX: U$1.82, UART.1
USBVCC: F2.2, TR1.1
USB_HOSTEN: R11.2, U$1.113
USHIELD: FB2.2, X3.BASE@1, X3.BASE@2, X3.SPRT@1, X3.SPRT@2, X3.SPRT@3, X3.SPRT@4
VBUS: F2.1, X3.VBUS
VDDCORE: C1.1, C8.2, C9.1, L1.P$1, U$1.115
VIN: C12.1, PC1.+, POWER.8, R1.1, T2.1, U1.3

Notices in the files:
parts and their libraries:
microbuilder: This work is placed in the public domain, and may be freely used for commercial and non-commercial work with the following conditions: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
SparkFun-Aesthetics: Licensing: CC v3.0 Share-Alike You are welcome to use this library for commercial purposes.
